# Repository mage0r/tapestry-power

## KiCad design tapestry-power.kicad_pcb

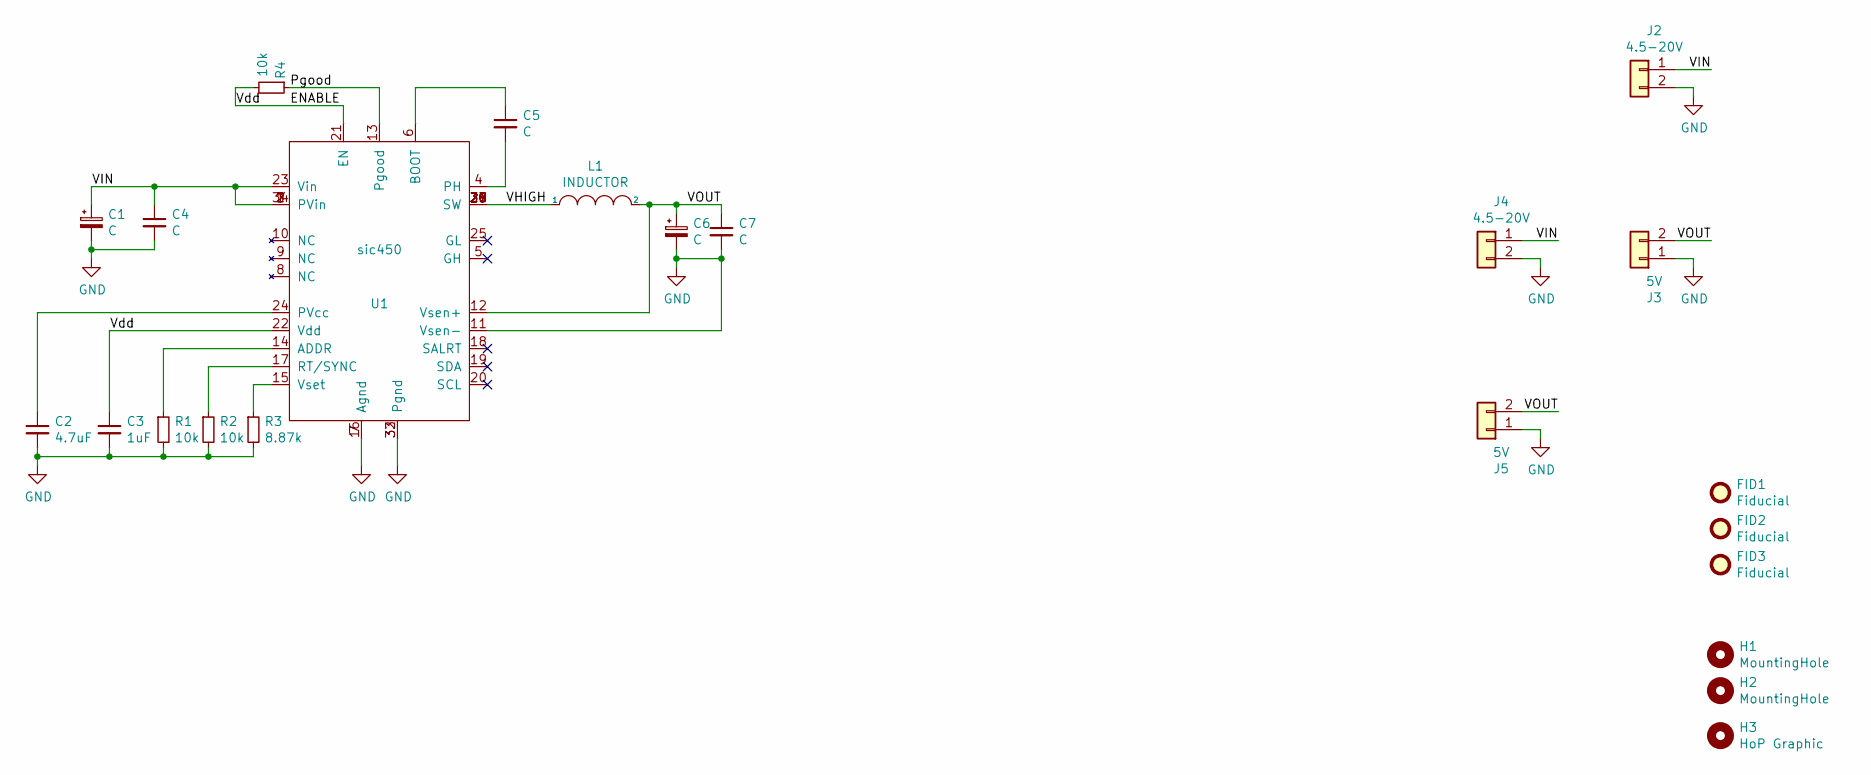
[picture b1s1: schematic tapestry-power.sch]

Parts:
C1, C6: C; CP_Elec_4x5.3
C2: 4.7uF; C_0805_2012Metric_Pad1.18x1.45mm_HandSolder
C3: 1uF; C_0805_2012Metric_Pad1.18x1.45mm_HandSolder
C4, C5: C; C_0805_2012Metric_Pad1.18x1.45mm_HandSolder
C7: C; C_0504_1310Metric_Pad0.83x1.28mm_HandSolder
FID1, FID2, FID3: Fiducial; Fiducial_0.5mm_Mask1mm
H1, H2: MountingHole; MountingHole_3.2mm_M3
H3: HoP Graphic; HoP_logo
J2: 4.5-20V; p2034a-dinkle-2-way-5mm
J3: 5V; p2034a-dinkle-2-way-5mm
J4: 4.5-20V; Solder-Nut.2x1
J5: 5V; Solder-Nut.2x1
L1: INDUCTOR; IP67GZ01
R1, R2, R4: 10k; R_0805_2012Metric_Pad1.20x1.40mm_HandSolder
R3: 8.87k; R_0805_2012Metric_Pad1.20x1.40mm_HandSolder; Voltage 8.87k = 5V. 11k = 12V
U1: sic450; MLP-34_EP_5x7_Pitch0.5mm_NonStandard

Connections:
/ENABLE: C3.1, R4.2, U1.21 (EN), U1.22 (Vdd)
/Pgood: R4.1, U1.13 (Pgood)
/VHIGH: L1.1, U1.26 (SW), U1.27 (SW), U1.28 (SW), U1.29 (SW), U1.30 (SW), U1.31 (SW)
/VIN: C1.1, C4.1, J2.1, J4.1, U1.1 (PVin), U1.2 (PVin), U1.3 (PVin), U1.23 (Vin), U1.34 (PVin)
/VOUT: C6.1, C7.1, J3.2, J5.2, L1.2, U1.12 (Vsen+)
GND: C1.2, C2.2, C3.2, C4.2, C6.2, C7.2, J2.2, J3.1, J4.2, J5.1, R1.2, R2.2, R3.2, U1.7 (Agnd), U1.11 (Vsen-), U1.16 (Agnd), U1.32 (Pgnd), U1.33 (Pgnd)
unnamed: C2.1, U1.24 (PVcc)
unnamed: C5.1, U1.6 (BOOT)
unnamed: C5.2, U1.4 (PH)
unnamed: R1.1, U1.14 (ADDR)
unnamed: R2.1, U1.17 (RT/SYNC)
unnamed: R3.1, U1.15 (Vset)

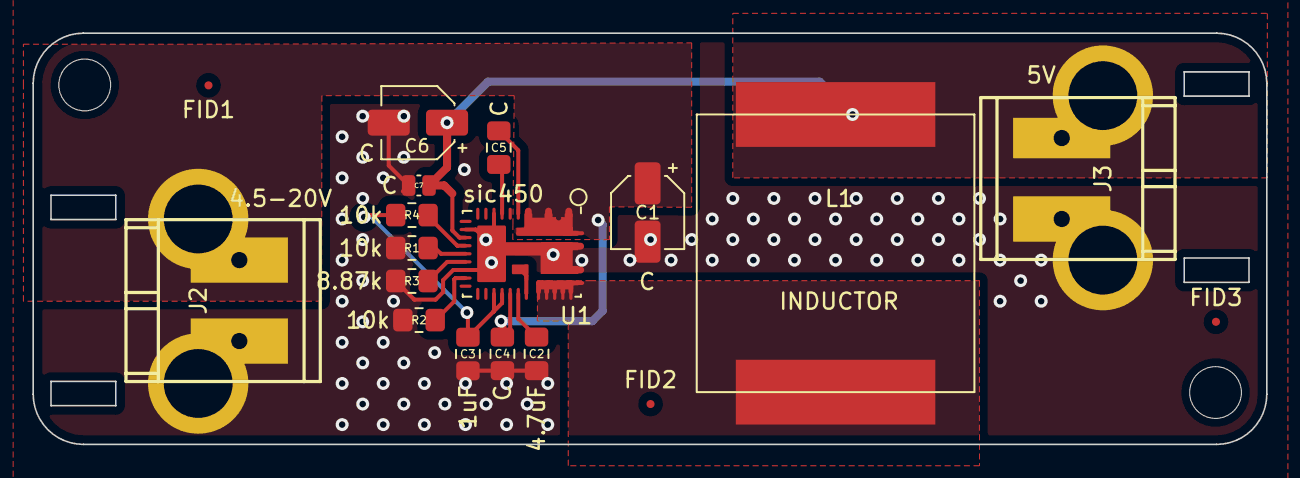
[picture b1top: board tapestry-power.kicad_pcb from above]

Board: 2 copper layers, 76.2 x 25.4 mm, 23 parts (1 on the bottom side), 12 nets.

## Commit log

2021-06-05 :lollipop: Added .gitattributes & .gitignore files
2021-06-05 Initial upload.
2021-06-05 Adding datasheets for the SiC450
2021-07-02 basic board
2021-07-02 Tightened up pours. Added Fiducials
2021-07-21 Added dual footprints for solder nuts.
2021-07-26 Updated board to wire in enable pin
    And included some relevant resistor and capacitor values.
